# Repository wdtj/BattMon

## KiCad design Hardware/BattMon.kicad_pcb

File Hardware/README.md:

# BattMon — RV battery monitor, revision I

Open **BattMon.kicad_pro** in KiCad 9 or 10, then open the schematic. **BattMon-schematic.pdf** is the printable drawing. This is a prototype module-wiring design with 32 assigned board-component footprints and bundled 3D models. It does not include a routed fabrication PCB or firmware. Footprint_Preview.kicad_pcb is an unrouted inventory board for 3D inspection only; see FOOTPRINTS_AND_MODELS.md for model provenance and mechanical verification limits.

## Parts and schematic fields

Every circuit component has the exact custom field **DigiKey Part Number**. Manufacturer, Manufacturer Part Number, Package and DigiKey URL are also populated. These fields are hidden on the drawing and available in Symbol Properties / the symbol-fields table. They are retained in the exported netlist.

- **BOM.csv** lists every reference, selected supplier SKU, package, quantity and fit status.
- **DigiKey_Shopping_List.csv** consolidates repeated supplier SKUs and omits DNP parts and external wiring points.
- **PART_SELECTIONS.md** provides clickable product links and explains substitutions.
- Supplier selections were checked on November 14, 2026. Check availability when ordering; no order has been placed.

All carrier-board discrete parts now use through-hole packages, including the TO-220 LM2575, inductor and axial TVS/catch diode. The ADS1115 is an assembled Adafruit breakout with solderable headers. The 5KP18A TVS has a 5 kW specified pulse rating; this does not establish survival of every vehicle transient.

U4 represents the complete XIAO/base assembly. Its main DigiKey Part Number field identifies the XIAO processor; separate Expansion Base DigiKey Part Number and Header DigiKey Part Number fields identify the base and headers. The BOM lists these as separate purchasing items. F1 has a separate Fuse Holder DigiKey Part Number field, and JP1 has a separate Shunt DigiKey Part Number field; those accessories also have purchasing rows.

The former high-current J2/J3 connection points are removed. The LM2575 buck supply is now on-board and J4 is removed. J5 connects the external XIAO/base assembly and J6 the external Tamura sensor. These carry monitor power/signals only. The discussed 277-6402-ND heavy-current terminal block is not required.

## Installation — external pass-through sensor

U2 is **Tamura L37S100S05M**, DigiKey **132-L37S100S05M-ND**, replacing ACS758. The existing insulated battery cable passes through the sensor's solid 20.4 x 10.4 mm aperture. It is **not split-core/clamp-on**: disconnect a cable end to install it. Measure the insulated cable and any lug before ordering/installation; the narrow opening is 10.4 mm. Do not strip insulation to make a cable fit. If the lug will not pass, safe professional retermination or a different split-core sensor is needed.

The cable remains the entire primary-current path. No battery charging/load current passes through the PCB, sensor signal connector, or J5/J6. Normal RV cable/fuse protection remains unchanged. Mount the sensor securely and protect its connector from moisture and strain. The sensor's temperature rating is -40 to +85 C; this is not the rating of the entire monitor assembly.

Choose one trunk conductor carrying all battery charge/discharge current. Either battery-positive or battery-negative can be measured. Do not include positive and negative together in the aperture, and make sure alternate battery connections do not bypass the sensed cable. Orient the indicated current direction to make charging positive; verify against a known charging/discharging condition and invert the firmware sign if necessary. Disconnect battery and charging sources before moving a cable end.

J1 remains a separate low-current voltage-sense/power connection: pin 1 to battery positive through F1 (1 A) at the battery takeoff, pin 2 to battery negative. The BATTERY_SIDE net now denotes that sense/power connection only.

Sensor pinout, low-current carrier headers and calibration are detailed in **SENSOR_WIRING.md**. The Tamura M variant has a Molex 22-04-1041 header. Sensor pin 1 is VREF and is intentionally unused; pin 2 is OUT, pin 3 GND, pin 4 +5 V. Leave housing cavity 1 empty. Do not connect VREF to ground or to 3V3.

Supply U2 from the regulated 5V net before D5/JP1, not from raw battery voltage or the XIAO/base power rail. Locate C3 near the sensor connector and use short, quiet signal wiring. The regulator must remain on for current readings even when the XIAO is powered by USB.

## Protected supply and XIAO expansion base

The selected base is Seeed **103030356**, DigiKey **1597-103030356-ND**. It requires a separately purchased standard **XIAO ESP32S3** (non-Sense) and suitable headers. It is represented as an external assembly rather than a reproduction of its internal circuitry. Its OLED can display measurements when firmware is added.

F1 protects the monitor power lead only; it does not protect the RV main current path. D1 (axial SB2100, 100 V / 2 A) provides reverse-polarity protection. D2 suppresses positive transients after D1. U1 is the LM2575-5.0WT 5 V / 1 A buck IC. L1 (330 uH) and D6 (MBR360) form its switching power stage; pin 4 senses the output after L1. Pin 5 is grounded for continuous operation. D2 is now a 5KP18A with 18 V standoff and 29.2 V maximum specified clamp. See POWER_SUPPLY.md for selection, thermal and layout requirements. C1/C2 provide input decoupling and C9/C10 provide output decoupling. Battery voltage is sensed before D1 so its forward drop does not create a measurement offset.

Actual clamp overshoot, wiring inductance, surge energy, thermal behavior and load-dump operation require bench validation. This is not an ISO 7637/ISO 16750 qualified design. Keep protection connections short and use the specified or higher voltage ratings. A destructive TVS fault may open F1.

D5 (axial 1N5819) provides series isolation in the XIAO/base 5 V feed, followed by JP1. Close JP1 for RV-powered operation. **Remove JP1 before USB power** to avoid simultaneously driving the shared USB/5 V rail. For valid live measurements during USB use, the RV regulator must still power the Hall sensor. USB-only power does not power that sensor; reject its readings.

Never connect RV 12 V to the base's 5 V header, Grove power pins or single-cell lithium battery socket. Leave the lithium battery socket empty. Turn the base switch on and verify its 3.3 V rail before attaching the ADC. The sensor uses the regulator's independent 5 V output, not the base servo-boost output.

| BattMon net | Expansion base location in published v1.0 schematic | XIAO signal |
| --- | --- | --- |
| 5V_ESP (after D5/JP1) | 5 V header, J11 pin 1 | 5V / VBUS |
| GND | Ground header, J11 pin 2 | GND |
| 3V3 | 3.3 V header, J11 pin 3 | Shared 3V3 rail |
| SDA | D4 header, J10 pin 5 | GPIO5 |
| SCL | D5 header, J10 pin 6 | GPIO6 |

Either base Grove I2C socket can alternatively supply SCL on pin 1, SDA on pin 2, 3V3 on pin 3 and GND on pin 4 in the published drawing. Follow the printed labels and connector orientation. Seeed has changed the PMIC under this SKU; verify connections against the actual revision supplied.

U4 schematic numbers 1..5 are functional identifiers, not physical header positions. Wire by the labels above. Other XIAO functions are unused in this prototype.

## ADS1115 breakout wiring

U3 is now **Adafruit 1085**, DigiKey **1528-1085-ND**, rather than a bare ADS1115IDGS. Its schematic pin identifiers are its printed breakout labels; do not use the old IC pin numbers.

| Breakout label | BattMon net / connection |
| --- | --- |
| VIN | 3V3 |
| GND | GND |
| SDA | SDA / XIAO D4 / GPIO5 |
| SCL | SCL / XIAO D5 / GPIO6 |
| ADDR | GND (address 0x48; leave optional address jumper open) |
| ALRT | Unconnected |
| A0 | HALL_ADC |
| A1 | VBAT_ADC |
| A2 | V5_ADC |
| A3 | GND |

If extra analog supply-output pads are present on the breakout, leave them unused. Follow its silkscreen rather than assuming a connector pin order. Its ADC chip and other SMD components are already assembled; solder only the header/wires required for this build.

The base has onboard I2C pull-ups. The Adafruit breakout also has 10 kOhm pull-ups to VIN; powering it at 3.3 V keeps both sets on the correct logic rail. R8/R9 remain **DNP** and are not in the shopping quantities. Do not power the ADC module from 5 V. For the XIAO ESP32S3, Arduino I2C initialization is `Wire.begin(5, 6)`.

The base OLED and RTC share I2C with the ADC. Published base addresses convert to 7-bit 0x3C and 0x51, distinct from ADC address 0x48. Confirm all attached devices with an I2C scan. No firmware is included.

## Measurement and calibration

Use single-ended ADS1115 conversions, PGA +/-4.096 V and 128 samples/s. The ADC supply is 3.3 V, and its input rails must still be respected. Read after switching channels has settled and average samples to reduce noise.

| Channel | Analog signal | Scaling / purpose |
| --- | --- | --- |
| A0 | Tamura OUT through R1/R2 | 0.6 times sensor output |
| A1 | Battery voltage through R5/R6/R7 | Battery / 16 |
| A2 | Regulator supply through R3/R4 | 0.6 times sensor supply; diagnostic only |

For this PGA, signed ADC code times 0.000125 gives volts. The sensor's nominal sensitivity is 0.625 V per 100 A, or 0.00625 V/A. With the existing 0.6 divider, A0 changes by **0.00375 V/A**. Current uses an absolute calibrated zero; **do not use the former ACS758 supply-ratio formula**.

- Battery volts = A1 volts * 16.
- Sensor supply volts = A2 volts / 0.6. Reject current measurements when this is outside 4.75-5.25 V.
- Current amps = direction_sign * (A0 volts - measured_zero_A0_volts) / 0.00375, before gain calibration.

At zero current, sensor OUT is approximately 2.5 V and A0 approximately 1.5 V. A0 is approximately 1.125 V at -100 A and 1.875 V at +100 A. These are nominal values; measure zero rather than hardcoding 1.5 V. Tamura specifies 100 A nominal and a larger measuring range, but this design is documented/calibrated for +/-100 A. Do not treat a sensor range as a cable/fuse rating.

Calibrate zero only when no current flows through the sensed cable. Power the monitor separately or account for its own battery consumption during that procedure. Then calibrate gain against a known current and voltage against a reliable meter. Store zero/gain in nonvolatile memory when firmware is added. Do not automatically zero during normal operation: that can erase a real battery current. Check charging/discharging sign.

Nominal ADC granularity is about 0.033 A/code. Actual accuracy is limited by sensor offset, hysteresis, temperature drift, noise, resistor tolerance and calibration. This sensor is not a precision instrument for integrating small standby loads over weeks. Normal voltage measurement is approximately 0-18 V; the divider's extra headroom is not approval to use a 48 V battery bank.

R5/R6 remain two 75 kOhm resistors, equivalent to 150 kOhm. All divider resistors are axial 0.1% parts. C8/C9 are polarized with positive to 3V3/5V respectively. The 100 nF capacitors use one 100 V through-hole X7R type for simpler purchasing.

D3/D4 BAT85S clamps limit ADC excursions at the small current set by the divider. They do not replace the TVS or constitute a tested transient withstand rating. The upper clamp may inject a small current into 3V3 with the sense lead attached and electronics off; remove F1 for storage/service.

Voltage and current alone do not establish reliable state of charge. Amp-hour tracking requires firmware, offset/gain calibration, elapsed-time integration and battery-specific synchronization. Assess continuous monitor/base/regulator drain and disconnect for long storage or design a low-power mode.

## Verification

KiCad 9.0.2 parsed the revised schematic and exported the PDF/netlists. ERC reports zero errors/warnings. All 15 nets and 85 wired component-pin connections were compared with an independently updated expected connection map; sensor VREF, J6 pin 1 and ADC ALRT are explicit no-connects. Supplier/footprint fields were checked in the exported netlist.

All 32 assigned footprints loaded successfully and their pad identifiers were checked against circuit pins. All relative model paths resolve to bundled files. The unrouted inspection board exported successfully to STEP with its component models. Generic visual models and assembly-height assumptions are identified in FOOTPRINTS_AND_MODELS.md. Exact external Tamura and XIAO/base STEP assemblies were not obtained and are not represented by substitute models.

The sensor, regulator, XIAO/base and inline fuse are external and excluded from PCB transfer; their carrier interfaces are explicit headers. Custom module symbols use passive pin types, so ERC cannot validate actual module power direction or internal behavior. These are file/connectivity/CAD checks, not bench tests, a completed PCB layout or automotive qualification. Complete placement, routing, mechanical/thermal checks and hardware validation before fabrication/installation.

## References

- Selected supplier product pages: see PART_SELECTIONS.md and BOM.csv.
- Tamura sensor datasheet: https://www.tamuracorp.com/global/products/download/pdf/L37SxxxS05_en.pdf
- TI ADS1115 datasheet: https://www.ti.com/lit/ds/symlink/ads1115.pdf
- Adafruit breakout pinouts: https://learn.adafruit.com/adafruit-4-channel-adc-breakouts/pinouts
- Microchip regulator: https://ww1.microchip.com/downloads/aemDocuments/documents/APID/ProductDocuments/DataSheets/LM2575-52kHz-Simple-1A-Buck-Regulator-DS20007078.pdf
- Seeed expansion base: https://wiki.seeedstudio.com/Seeeduino-XIAO-Expansion-Board/
- XIAO ESP32S3: https://wiki.seeedstudio.com/xiao_esp32s3_getting_started/

## Revision I — discrete buck and phone connection

U1 is Microchip LM2575-5.0WT, DigiKey 576-1516-5-ND. L1 is Wurth 7447480331, D6 is Panjit MBR360, C9 is Panasonic EEU-FC1E331 (330 uF / 25 V), and D2 is Littelfuse 5KP18A. These replace the external RECOM module and its J4 interface. Supplier fields, footprints, model assignments, BOM and shopping list have been updated. See POWER_SUPPLY.md for design calculations and the required hardware checks. This remains an unrouted prototype schematic, not a fabrication-ready PCB.

The ESP32S3 supports Bluetooth Low Energy, suitable for a custom Android or iPhone app. It does not support Bluetooth Classic/SPP serial connections. Plan a BLE GATT peripheral on BattMon with the phone as central. Notify battery voltage, signed charge/discharge current, sensor-supply voltage and measurement/calibration status about once per second. Continue monitoring when disconnected. Require an explicit user action and authenticated connection for calibration changes. Place the antenna outside a metal battery enclosure or verify RF performance in the final installation.

This revision documents the intended BLE interface; neither BLE firmware nor a phone app is included. State of charge requires a separate battery-specific estimation/calibration design and is not inferred directly from current.

BLE reference: https://docs.espressif.com/projects/esp-idf/en/latest/esp32s3/api-guides/ble/overview.html

## External fuse and Tamura cable plug

The drawing now places F1 in a dashed EXTERNAL section with the existing RV battery BT1. The wiring order is battery positive -> F1 (1 A, at battery takeoff) -> supply cable -> J1 pin 1 -> board. Battery negative goes directly to J1 pin 2. J1 pin 1 is wired continuously to D1; its BAT_FUSED net also feeds the voltage divider. F1/holder are not mounted on the carrier PCB. BT1 is an existing installation item excluded from the BOM and PCB.

J7 is the sensor-end Molex 0022011042 housing (WM2022-ND), explicitly shown in the schematic with contact ordering fields and visible callouts. Fit three Molex 0008500160 contacts (WM16517-ND, 22-30 AWG) in cavities 2 OUT, 3 GND and 4 +5 V; leave cavity 1 VREF empty. These contacts replace the obsolete 0008500114 selection. J7-CONTACTS is a separate quantity-three BOM row, not another housing. J7 is a cable plug, so no carrier-board footprint is assigned. J6 remains the carrier end of the harness; verify the two connector families and pin orientation before applying power.

## Revision I drawing clarification

J1 is drawn as a two-contact terminal block with continuous wires through each electrical contact: battery positive -> external F1 -> J1.1 -> D1 -> buck input, and battery negative -> J1.2 -> PCB ground. Each circle is a single terminal/contact node, not an extra pin. Physical footprint pins remain 1 and 2.

The Hall output is now visibly wired U2 OUT -> J7.2 -> three-wire cable -> J6.2 -> R1/R2 divider -> ADS1115 A0. J7 is the external sensor-end plug, and J6 is the carrier header at the other end of the cable; they are different connector families and do not mate directly to each other. Ground and 5 V are drawn across cable contacts 3 and 4, with supply labels at the sensor and carrier. Cavity 1 remains unused at both ends. J7 housing/contact ordering callouts remain on the drawing. This changes presentation only; the verified electrical connectivity, BOM quantities and footprints remain unchanged.

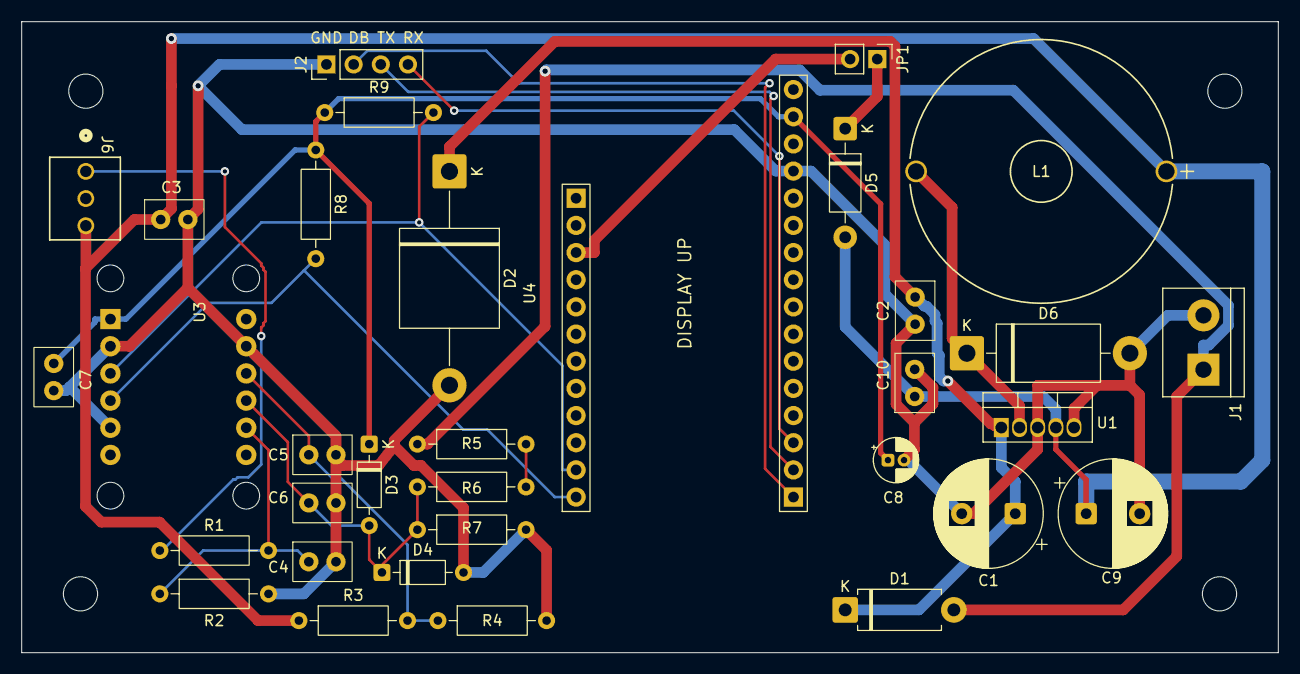
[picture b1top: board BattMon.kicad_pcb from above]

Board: 2 copper layers, 117.5 x 59.0 mm, 37 parts (0 on the bottom side), 18 nets.

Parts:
C1: 100 uF; CP_Radial_D10_P5
C2, C3, C4, C5, C6, C7, C10: 100 nF; KEMET_C320_Radial_P2.54
C8: 10 uF; CP_Radial_D4_P1.5
C9: 330 uF; CP_Radial_D10_P5
D1: SB2100; D_DO15_P10.16
D2: 5KP18A; D_P600_P20
D3, D4: BAT85S; D_DO35_P7.62
D5: 1N5819; D_DO41_P10.16
D6: MBR360; D_DO201AD_P15.24
H1, H2, H3, H4: MountingHole_3.2mm_M3
J1: Battery sense / power; Terminal_2P_P5.08
J2: Debug UART; Header_1x4_P2.54
J6: Hall Sensor; CONN_A-6373-03A_MOL
JP1: USB power isolate; Header_1x2_P2.54
L1: 300 uH / 3 A; 1430430C_MUR
R1, R3, R7: 10.0 k; R_Axial_6.3mm_P10.16
R2, R4: 15.0 k; R_Axial_6.3mm_P10.16
R5, R6: 75.0 k; R_Axial_6.3mm_P10.16
R8, R9: 4.7 k DNP; R_Axial_6.3mm_P10.16
U1: LM2575-5.0WT; TO220_5_Vertical
U3: Adafruit 1085 / ADS1115; Adafruit_1085_STEMMA_QT
U4: ESP32S3 Reverse TFT Feather; Adafruit_5691_Reverse_TFT_Feather_DisplayUp

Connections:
/3V3: C7.1, C8.1, D3.1 (K), R8.1, R9.1, U3.VIN, U4.15 (3.3V)
/5V: C3.1, C9.1, C10.1, D5.2 (A), J6.3, L1.1, R3.1, U1.4 (FB)
/5V_ESP: JP1.2 (B), U4.23 (USB)
/5V_ISO: D5.1 (K), JP1.1 (A)
/BAT_FUSED: D1.2 (A), J1.1, R5.1
/DBG_TX: J2.2, U4.1 (TDX0)
/HALL_ADC: C4.1, R1.2, R2.1, U3.A0
/HALL_OUT: J6.1, R1.1
/SCL: R9.2, U3.SCL, U4.31 (SCL)
/SDA: R8.2, U3.SDA, U4.32 (SDA)
/SW: D6.1 (K), L1.2, U1.2 (SW)
/UART_RX: J2.4, U4.3 (RX)
/UART_TX: J2.3, U4.2 (TX)
/V5_ADC: C5.1, R3.2, R4.1, U3.A2
/VBAT_ADC: C6.1, D3.2 (A), D4.1 (K), R6.2, R7.1, U3.A1
/VBAT_PROT: C1.1, C2.1, D1.1 (K), D2.1 (K), U1.1 (VIN)
/V_DIV_MID: R5.2, R6.1
GND: C1.2, C2.2, C3.2, C4.2, C5.2, C6.2, C7.2, C8.2, C9.2, C10.2, D2.2 (A), D4.2 (A), D6.2 (A), J1.2, J2.1, J6.2, R2.2, R4.2, R7.2, U1.3 (GND), U1.5 (ON/OFF), U3.A3, U3.ADDR, U3.GND, U4.13 (GND)
